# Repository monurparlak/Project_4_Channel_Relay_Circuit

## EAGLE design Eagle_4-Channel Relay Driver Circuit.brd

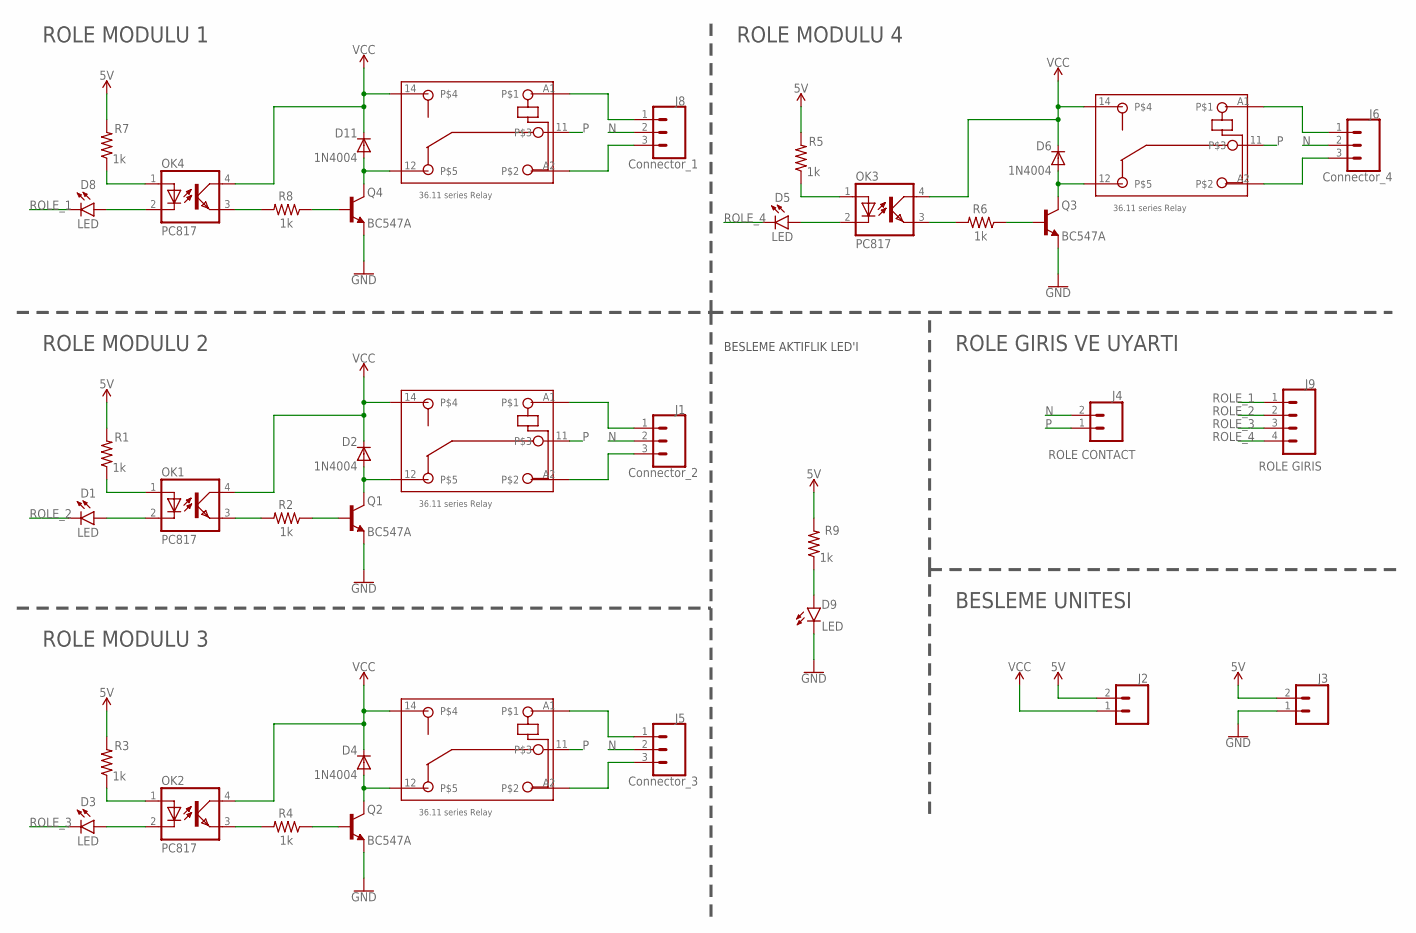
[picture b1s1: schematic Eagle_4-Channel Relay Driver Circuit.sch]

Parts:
D1, D3, D5, D8, D9: LED; LED_3MM
D2, D4, D6, D11: 1N4004; DO41-10
J1: Connector_2; 1X03
J2, J3: CONN_02; 1X02
J4: ROLE CONTACT; 1X02
J5: Connector_3; 1X03
J6: Connector_4; 1X03
J8: Connector_1; 1X03
J9: ROLE GIRIS; 1X04
OK1, OK2, OK3, OK4: PC817; DIL04
Q1, Q2, Q3, Q4: BC547A; TO-92
R1, R2, R3, R4, R5, R6, R7, R8, R9: 1k; 0207/10
ROLE_1, ROLE_2, ROLE_3, ROLE_4: 36.11

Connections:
5V: J2.2, J3.2, R1.2, R3.2, R5.2, R7.2, R9.2
GND: D9.K (C), J3.1, Q1.1 (E), Q2.1 (E), Q3.1 (E), Q4.1 (E)
N: J1.2, J4.2, J5.2, J6.2, J8.2
unnamed: OK1.1 (A), R1.1
unnamed: Q1.2 (B), R2.1
unnamed: D2.A, Q1.3 (C), ROLE_2.12
unnamed: D1.A, OK1.2 (C)
unnamed: OK1.3 (EMIT), R2.2
unnamed: J1.1, ROLE_2.A1
unnamed: J1.3, ROLE_2.A2
unnamed: OK2.1 (A), R3.1
unnamed: Q2.2 (B), R4.1
unnamed: D4.A, Q2.3 (C), ROLE_3.12
unnamed: D3.A, OK2.2 (C)
unnamed: OK2.3 (EMIT), R4.2
unnamed: J5.1, ROLE_3.A1
unnamed: J5.3, ROLE_3.A2
unnamed: OK3.1 (A), R5.1
unnamed: Q3.2 (B), R6.1
unnamed: D6.A, Q3.3 (C), ROLE_4.12
unnamed: D5.A, OK3.2 (C)
unnamed: OK3.3 (EMIT), R6.2
unnamed: J6.1, ROLE_4.A1
unnamed: J6.3, ROLE_4.A2
unnamed: OK4.1 (A), R7.1
unnamed: Q4.2 (B), R8.1
unnamed: D11.A, Q4.3 (C), ROLE_1.12
unnamed: D8.A, OK4.2 (C)
unnamed: OK4.3 (EMIT), R8.2
unnamed: J8.1, ROLE_1.A1
unnamed: J8.3, ROLE_1.A2
unnamed: D9.A, R9.1
P: J4.1, ROLE_1.11, ROLE_2.11, ROLE_3.11, ROLE_4.11
ROLE_1: D8.K (C), J9.1
ROLE_2: D1.K (C), J9.2
ROLE_3: D3.K (C), J9.3
ROLE_4: D5.K (C), J9.4
VCC: D2.C, D4.C, D6.C, D11.C, J2.1, OK1.4 (COL), OK2.4 (COL), OK3.4 (COL), OK4.4 (COL), ROLE_1.14, ROLE_2.14, ROLE_3.14, ROLE_4.14

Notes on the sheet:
ROLE MODULU 1
ROLE MODULU 2
ROLE MODULU 3
ROLE MODULU 4
ROLE GIRIS VE UYARTI
BESLEME UNITESI
BESLEME AKTIFLIK LED'I

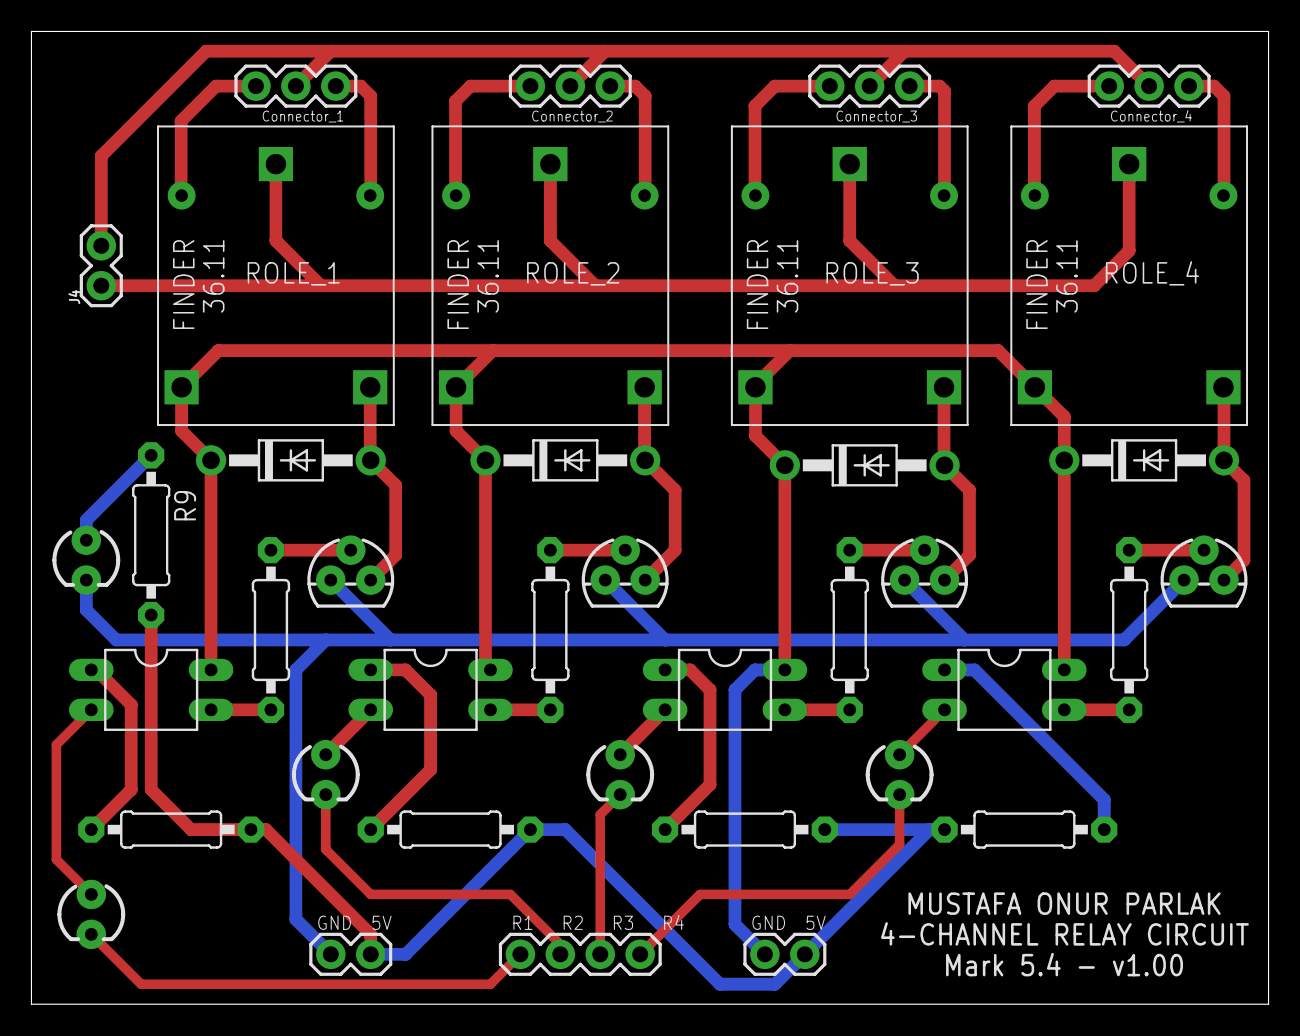
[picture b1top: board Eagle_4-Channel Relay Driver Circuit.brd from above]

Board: 2 copper layers, 78.7 x 61.9 mm, 38 parts (0 on the bottom side), 38 nets.

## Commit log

2020-07-05 Add files via upload
    This project includes the use of 4-channel relay, working principle, EAGLE circuit diagram, GERBER file and a sample Arduino code implementation.

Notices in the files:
parts and their libraries:
SparkFun-LED: Licensing: Creative Commons ShareAlike 4.0 International - https://creativecommons.org/licenses/by-sa/4.0
